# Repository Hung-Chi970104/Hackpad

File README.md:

## Components
- Seeed XIAO RP2040
- MX-Style switches x 9
- OLED display
- 3D PRINTED CASE

## Images
- 
- 
- 
-

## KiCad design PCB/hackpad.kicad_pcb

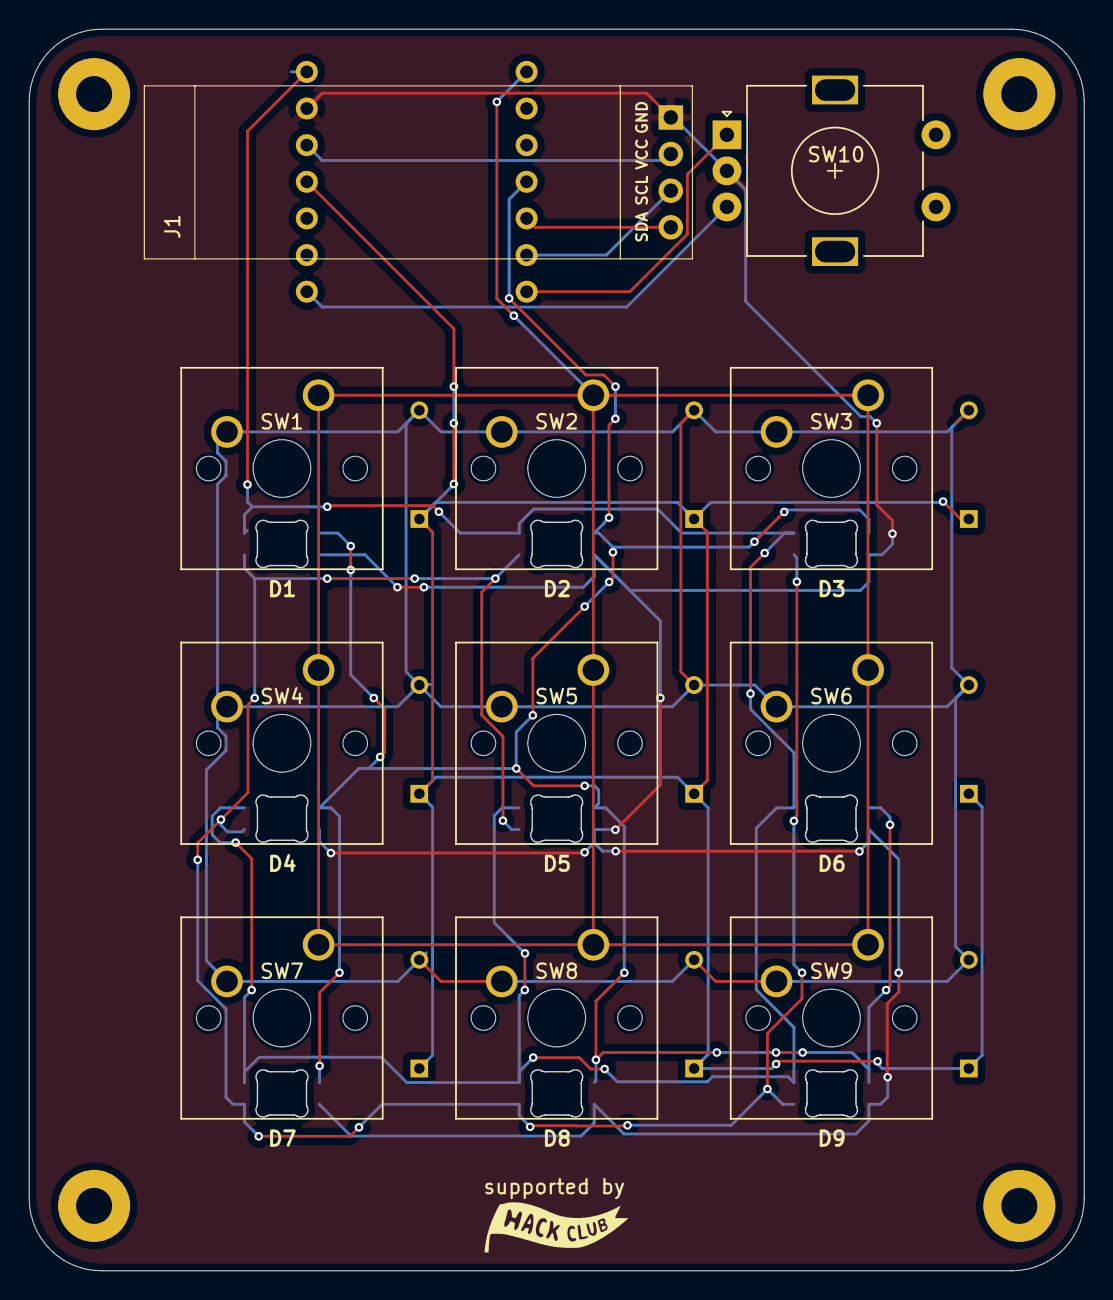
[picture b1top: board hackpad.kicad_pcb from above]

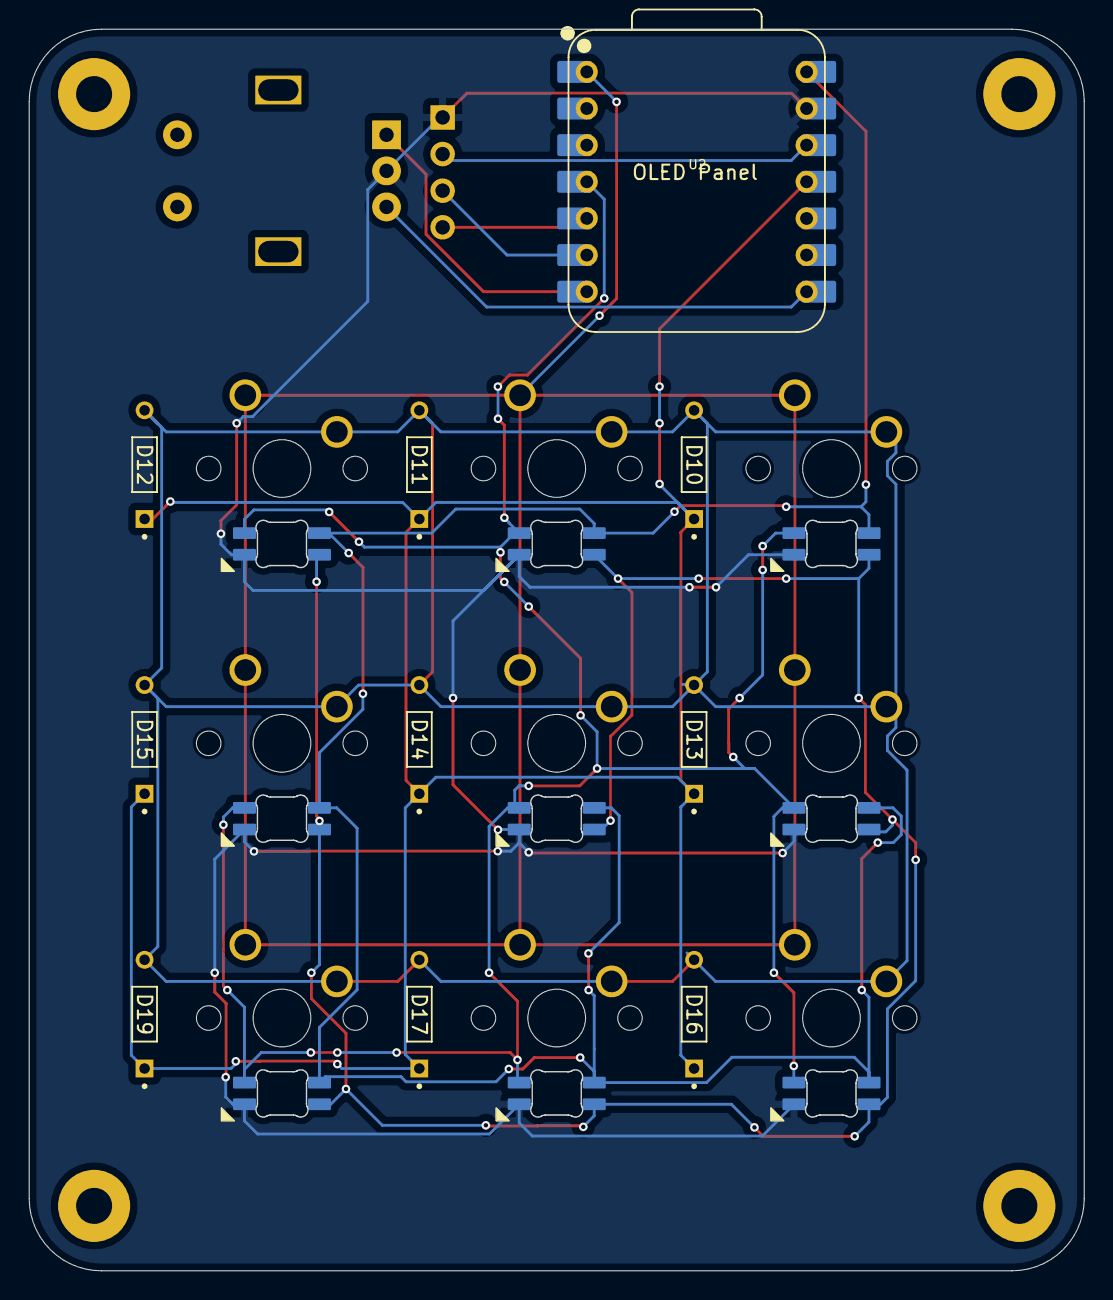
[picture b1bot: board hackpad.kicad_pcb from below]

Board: 2 copper layers, 73.1 x 86.1 mm, 34 parts (10 on the bottom side), 12 nets.

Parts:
D1, D2, D3, D4, D5, D6, D7, D8, D9: SK6812MINI-E; SK6812MINI-E_fixed
D10, D11, D12, D13, D14, D15, D16, D17, D19: 1N4148; DIOAD753W49L380D172B
H1, H2, H3, H4: MountingHole_Pad; MountingHole_2.5mm_Pad
J1: SSD1306; SSD1306-0.91-OLED-4pin-128x32
SW1, SW2, SW3, SW4, SW5, SW6, SW7, SW8, SW9: SW_Push_45deg; SW_Cherry_MX_1.00u_PCB
SW10: RotaryEncoder_Switch; RotaryEncoder_Alps_EC11E-Switch_Vertical_H20mm
U2: MOUDLE-SEEEDUINO-XIAO; XIAO-RP2040-DIP

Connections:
+3.3V: J1.2, U2.12 (3V3)
+5V: D1.1 (VDD), D2.1 (VDD), D3.1 (VDD), D4.1 (VDD), D5.1 (VDD), D6.1 (VDD), D7.1 (VDD), D8.1 (VDD), D9.1 (VDD), U2.14 (5V)
/Col 0: SW1.1, SW2.1, SW3.1, SW4.1, SW5.1, SW6.1, SW7.1, SW8.1, SW9.1, U2.1 (PA02_A0_D0)
/DIN: D1.4 (DIN), D2.4 (DIN), D3.4 (DIN), D4.4 (DIN), D5.4 (DIN), D6.4 (DIN), D7.4 (DIN), D8.4 (DIN), D9.4 (DIN), U2.4 (PA11_A3_D3)
/OUT A: SW10.A, U2.7 (PB08_A6_D6_TX)
/OUT B: SW10.B, U2.8 (PB09_A7_D7_RX)
/Row 0: D10.K, D11.K, D12.K, D13.K, D14.K, D15.K, D16.K, D17.K, D19.K, U2.11 (PA6_A10_D10_MOSI)
/SCL: J1.3, U2.6 (PA9_A5_D5_SCL)
/SDA: J1.4, U2.5 (PA8_A4_D4_SDA)
GND: D1.3 (VSS), D2.3 (VSS), D3.3 (VSS), D4.3 (VSS), D5.3 (VSS), D6.3 (VSS), D7.3 (VSS), D8.3 (VSS), D9.3 (VSS), J1.1, SW10.C, U2.13 (GND)
unnamed: D1.2 (DOUT), D2.2 (DOUT), D3.2 (DOUT), D4.2 (DOUT), D5.2 (DOUT), D6.2 (DOUT), D7.2 (DOUT), D8.2 (DOUT), D9.2 (DOUT)
unnamed: D10.A, D11.A, D12.A, D13.A, D14.A, D15.A, D16.A, D17.A, D19.A, SW1.2, SW2.2, SW3.2, SW4.2, SW5.2, SW6.2, SW7.2, SW8.2, SW9.2

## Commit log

2025-12-25 Update everything
2025-12-25 Added Step File
2026-01-18 Remove introductory section from README
    Removed introductory text about the hackpad.
